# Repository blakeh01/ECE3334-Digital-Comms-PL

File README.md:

# ECE3334: Digital Communications Project Lab

Implement and design a 16 QAM modulator that can transmit text using radios.

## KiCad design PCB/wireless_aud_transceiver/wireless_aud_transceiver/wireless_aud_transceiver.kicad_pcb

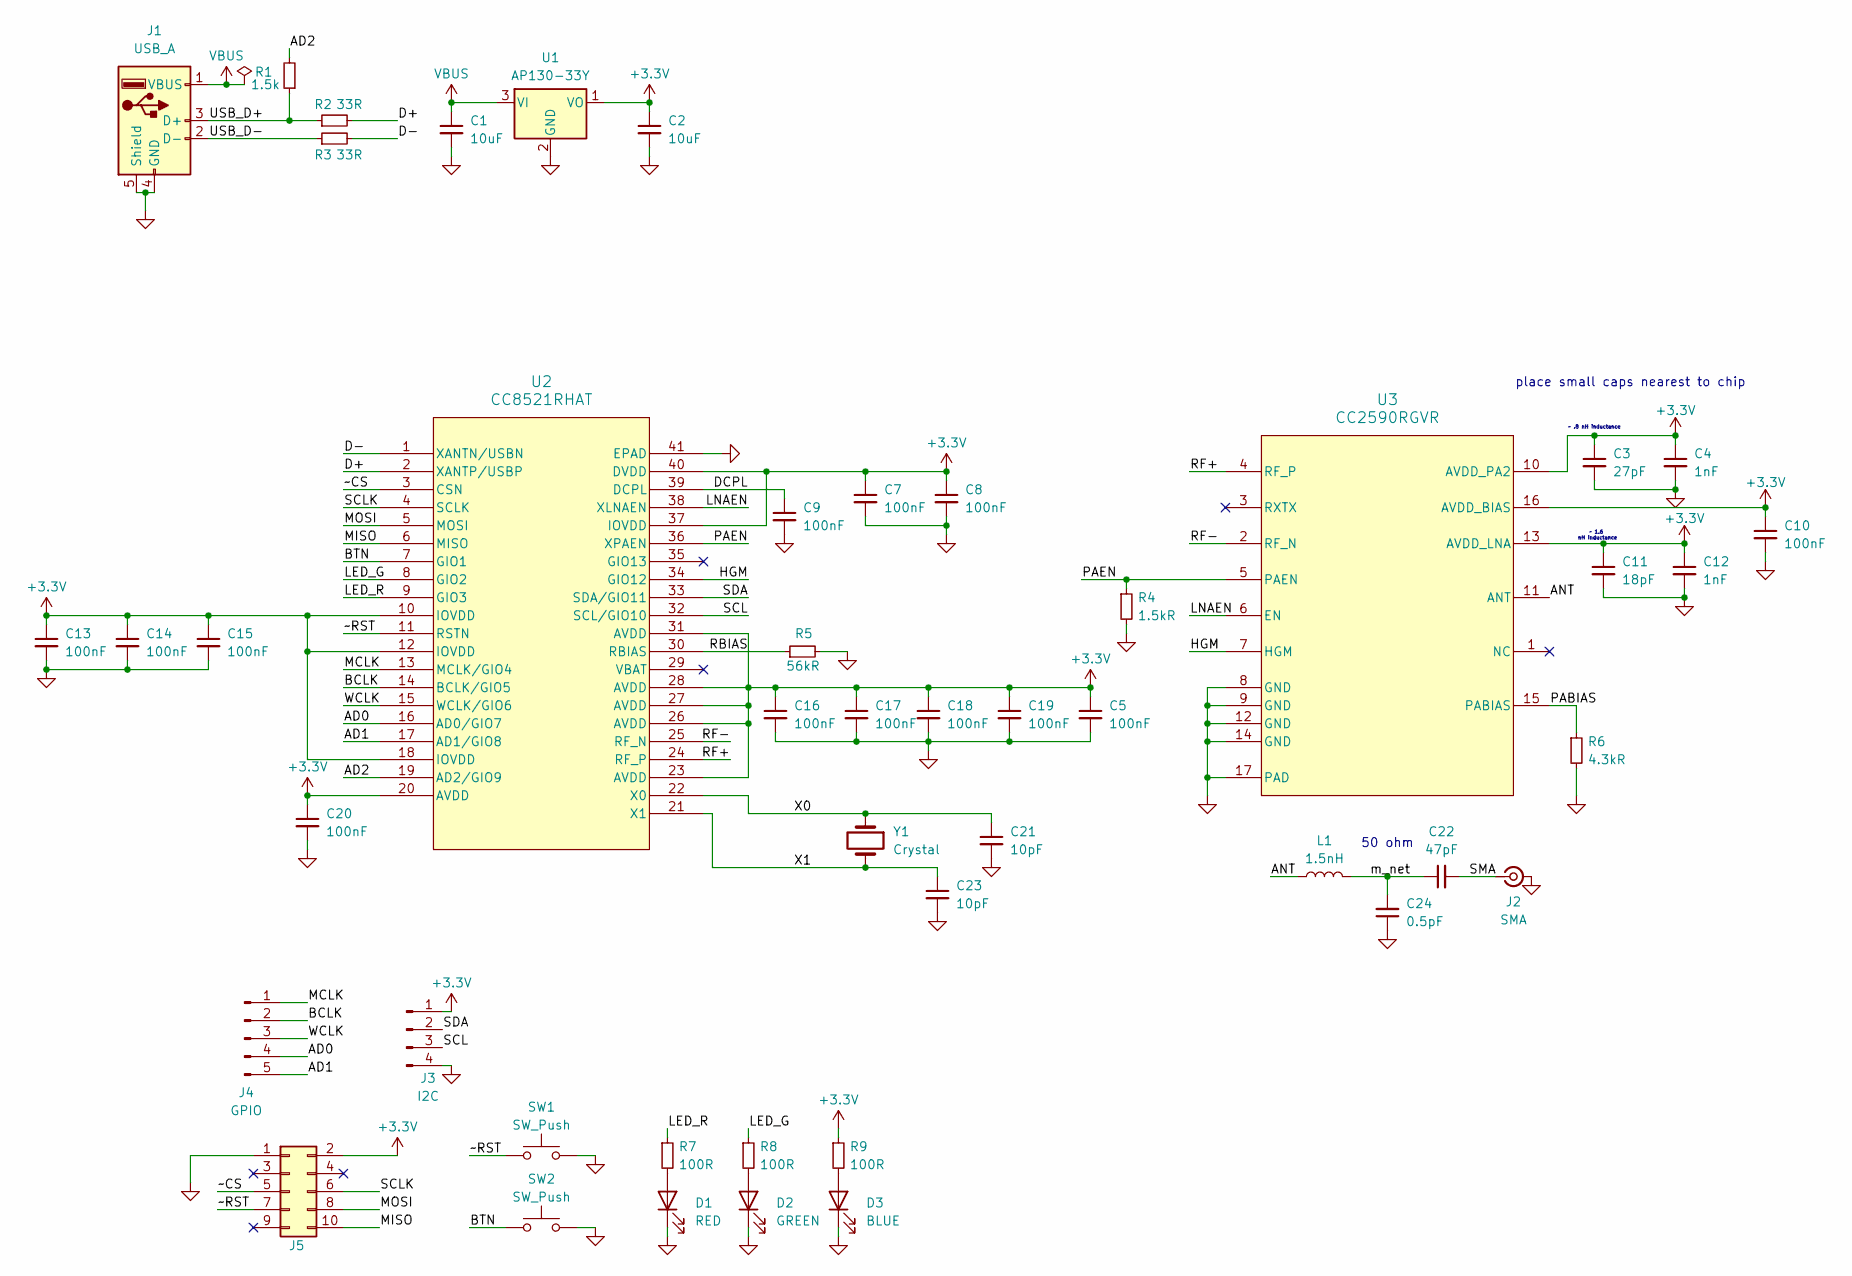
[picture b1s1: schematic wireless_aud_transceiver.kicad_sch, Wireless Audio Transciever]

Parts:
C1, C2: 10uF; C_0603_1608Metric
C3: 27pF; C_0402_1005Metric
C4, C12: 1nF; C_0402_1005Metric
C5, C7, C8, C9, C10, C13, C14, C15, C16, C17, C18, C19, C20: 100nF; C_0402_1005Metric
C11: 18pF; C_0402_1005Metric
C21, C23: 10pF; C_0402_1005Metric
C22: 47pF; C_0402_1005Metric
C24: 0.5pF; C_0402_1005Metric
D1: RED; LED_0603_1608Metric
D2: GREEN; LED_0603_1608Metric
D3: BLUE; LED_0603_1608Metric
J1: USB_A; USB_A_TE_292303-7_Horizontal
J2: SMA; SMA_Molex_73251-1153_EdgeMount_Horizontal
J3: I2C; PinHeader_1x04_P2.54mm_Vertical
J4: GPIO; PinHeader_1x05_P2.54mm_Vertical
J5: CC Debug; PinHeader_2x05_P2.54mm_Vertical
L1: 1.5nH; L_0402_1005Metric
R1: 1.5k; R_0402_1005Metric
R2, R3: 33R; R_0603_1608Metric
R4: 1.5kR; R_0402_1005Metric
R5: 56kR; R_0805_2012Metric
R6: 4.3kR; R_0402_1005Metric
R7, R8, R9: 100R; R_0402_1005Metric
SW1, SW2: SW_Push; SW_SPST_CK_RS282G05A3
U1: AP130-33Y; SOT-89-3
U2: CC8521RHAT; RHA40_4P5X4P5
U3: CC2590RGVR; RGV0016A
Y1: Crystal; Crystal_SMD_3225-4Pin_3.2x2.5mm

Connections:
/AD0: J4.4, U2.16 (AD0/GIO7)
/AD1: J4.5, U2.17 (AD1/GIO8)
/AD2: R1.2, U2.19 (AD2/GIO9)
/ANT: L1.1, U3.11 (ANT)
/BCLK: J4.2, U2.14 (BCLK/GIO5)
/BTN: SW2.1, U2.7 (GIO1)
/D+: R2.2, U2.2 (XANTP/USBP)
/D-: R3.2, U2.1 (XANTN/USBN)
/DCPL: C9.1, U2.39 (DCPL)
/HGM: U2.34 (GIO12), U3.7 (HGM)
/LED_G: R8.1, U2.8 (GIO2)
/LED_R: R7.1, U2.9 (GIO3)
/LNAEN: U2.38 (XLNAEN), U3.6 (EN)
/MCLK: J4.1, U2.13 (MCLK/GIO4)
/MISO: J5.10, U2.6 (MISO)
/MOSI: J5.8, U2.5 (MOSI)
/PABIAS: R6.1, U3.15 (PABIAS)
/PAEN: R4.1, U2.36 (XPAEN), U3.5 (PAEN)
/RF+: U2.24 (RF_P), U3.4 (RF_P)
/RF-: U2.25 (RF_N), U3.2 (RF_N)
/SCL: J3.3, U2.32 (SCL/GIO10)
/SCLK: J5.6, U2.4 (SCLK)
/SDA: J3.2, U2.33 (SDA/GIO11)
/SMA: C22.2, J2.1 (In)
/USB_D+: J1.3 (D+), R1.1, R2.1
/USB_D-: J1.2 (D-), R3.1
/WCLK: J4.3, U2.15 (WCLK/GIO6)
/X0: C21.1, U2.22 (X0), Y1.1
/X1: C23.1, U2.21 (X1), Y1.2
/m_net: C22.1, C24.2, L1.2
/~CS: J5.5, U2.3 (CSN)
/~RST: J5.7, SW1.1, U2.11 (RSTN)
GND: C1.2, C2.2, C3.2, C4.2, C5.2, C7.2, C8.2, C9.2, C10.2, C11.2, C12.2, C13.2, C14.2, C15.2, C16.2, C17.2, C18.2, C19.2, C20.2, C21.2, C23.2, C24.1, D1.1 (K), D2.1 (K), D3.1 (K), J1.4 (GND), J1.5 (Shield), J2.2 (Ext), J3.4, J5.1, R4.2, R5.2, R6.2, SW1.2, SW2.2, U1.2 (GND), U2.41 (EPAD), U3.8 (GND), U3.9 (GND), U3.12 (GND), U3.14 (GND), U3.17 (PAD)
unnamed: D1.2 (A), R7.2
unnamed: D2.2 (A), R8.2
unnamed: D3.2 (A), R9.2
VBUS: C1.1, J1.1 (VBUS), U1.3 (VI)

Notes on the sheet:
place small caps nearest to chip
~ .8 nH inductance
~ 1.6 nH inductance
50 ohm

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
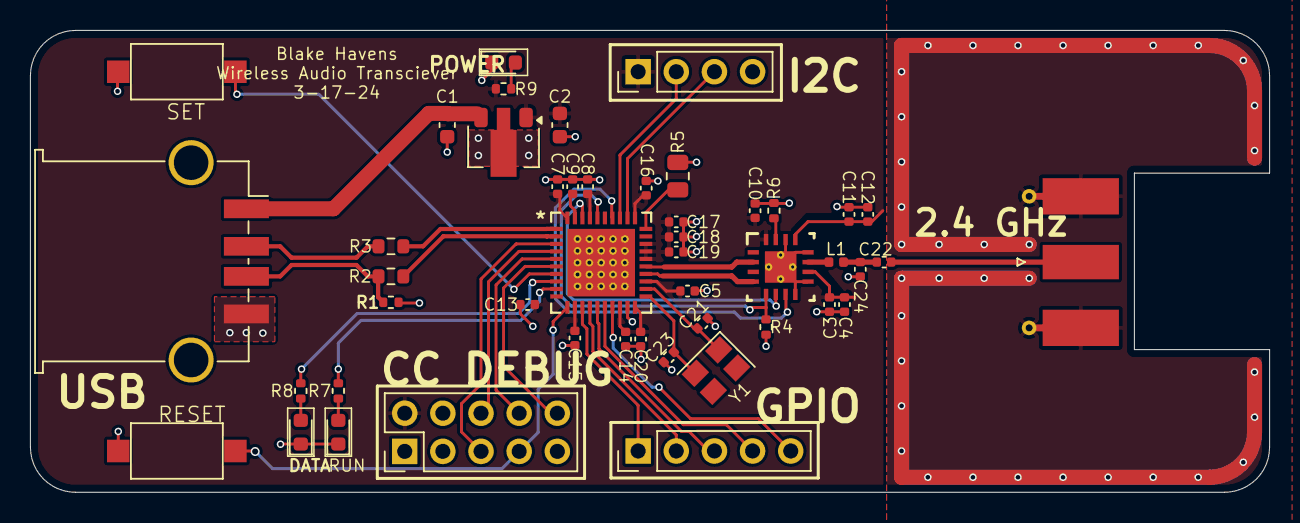
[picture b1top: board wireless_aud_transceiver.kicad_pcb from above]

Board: 4 copper layers, 82.5 x 30.8 mm, 47 parts (0 on the bottom side), 39 nets.

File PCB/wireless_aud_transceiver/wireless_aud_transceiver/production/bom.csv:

Designator,Footprint,Quantity,Value,LCSC Part #
48 MHz,Crystal_SMD_3225-4Pin_3.2x2.5mm,1,Crystal,
"C1, C2",0603,2,10uF,
"C10, C13, C14, C15, C16, C17, C18, C19, C20, C5, C7, C8, C9",0402,13,100nF,
C11,0402,1,18pF,
"C12, C4",0402,2,1nF,
"C21, C23",0402,2,10pF,
C22,0402,1,47pF,
C24,0402,1,0.5pF,
C3,0402,1,27pF,
D1,0603,1,RED,
D2,0603,1,GREEN,
D3,0603,1,BLUE,
J1,USB_A_TE_292303-7_Horizontal,1,USB_A,
J2,SMA_Molex_73251-1153_EdgeMount_Horizontal,1,SMA,
J3,PinHeader_1x04_P2.54mm_Vertical,1,I2C,
J4,PinHeader_1x05_P2.54mm_Vertical,1,GPIO,
J5,PinHeader_2x05_P2.54mm_Vertical,1,CC Debug,
L1,0402,1,1.5nH,
R1,0603,1,1.5k,
"R2, R3",0603,2,33R,
R4,0402,1,1kR,
R5,0805,1,56kR,
R6,0402,1,4.3kR,
"R7, R8, R9",0402,3,100R,
"SW1, SW2",SW_SPST_CK_RS282G05A3,2,SW_Push,
U1,SOT-89-3,1,AP130-33Y,
U2,RHA40_4P5X4P5,1,CC8521RHAT,
U3,RGV0016A,1,CC2590RGVR,
